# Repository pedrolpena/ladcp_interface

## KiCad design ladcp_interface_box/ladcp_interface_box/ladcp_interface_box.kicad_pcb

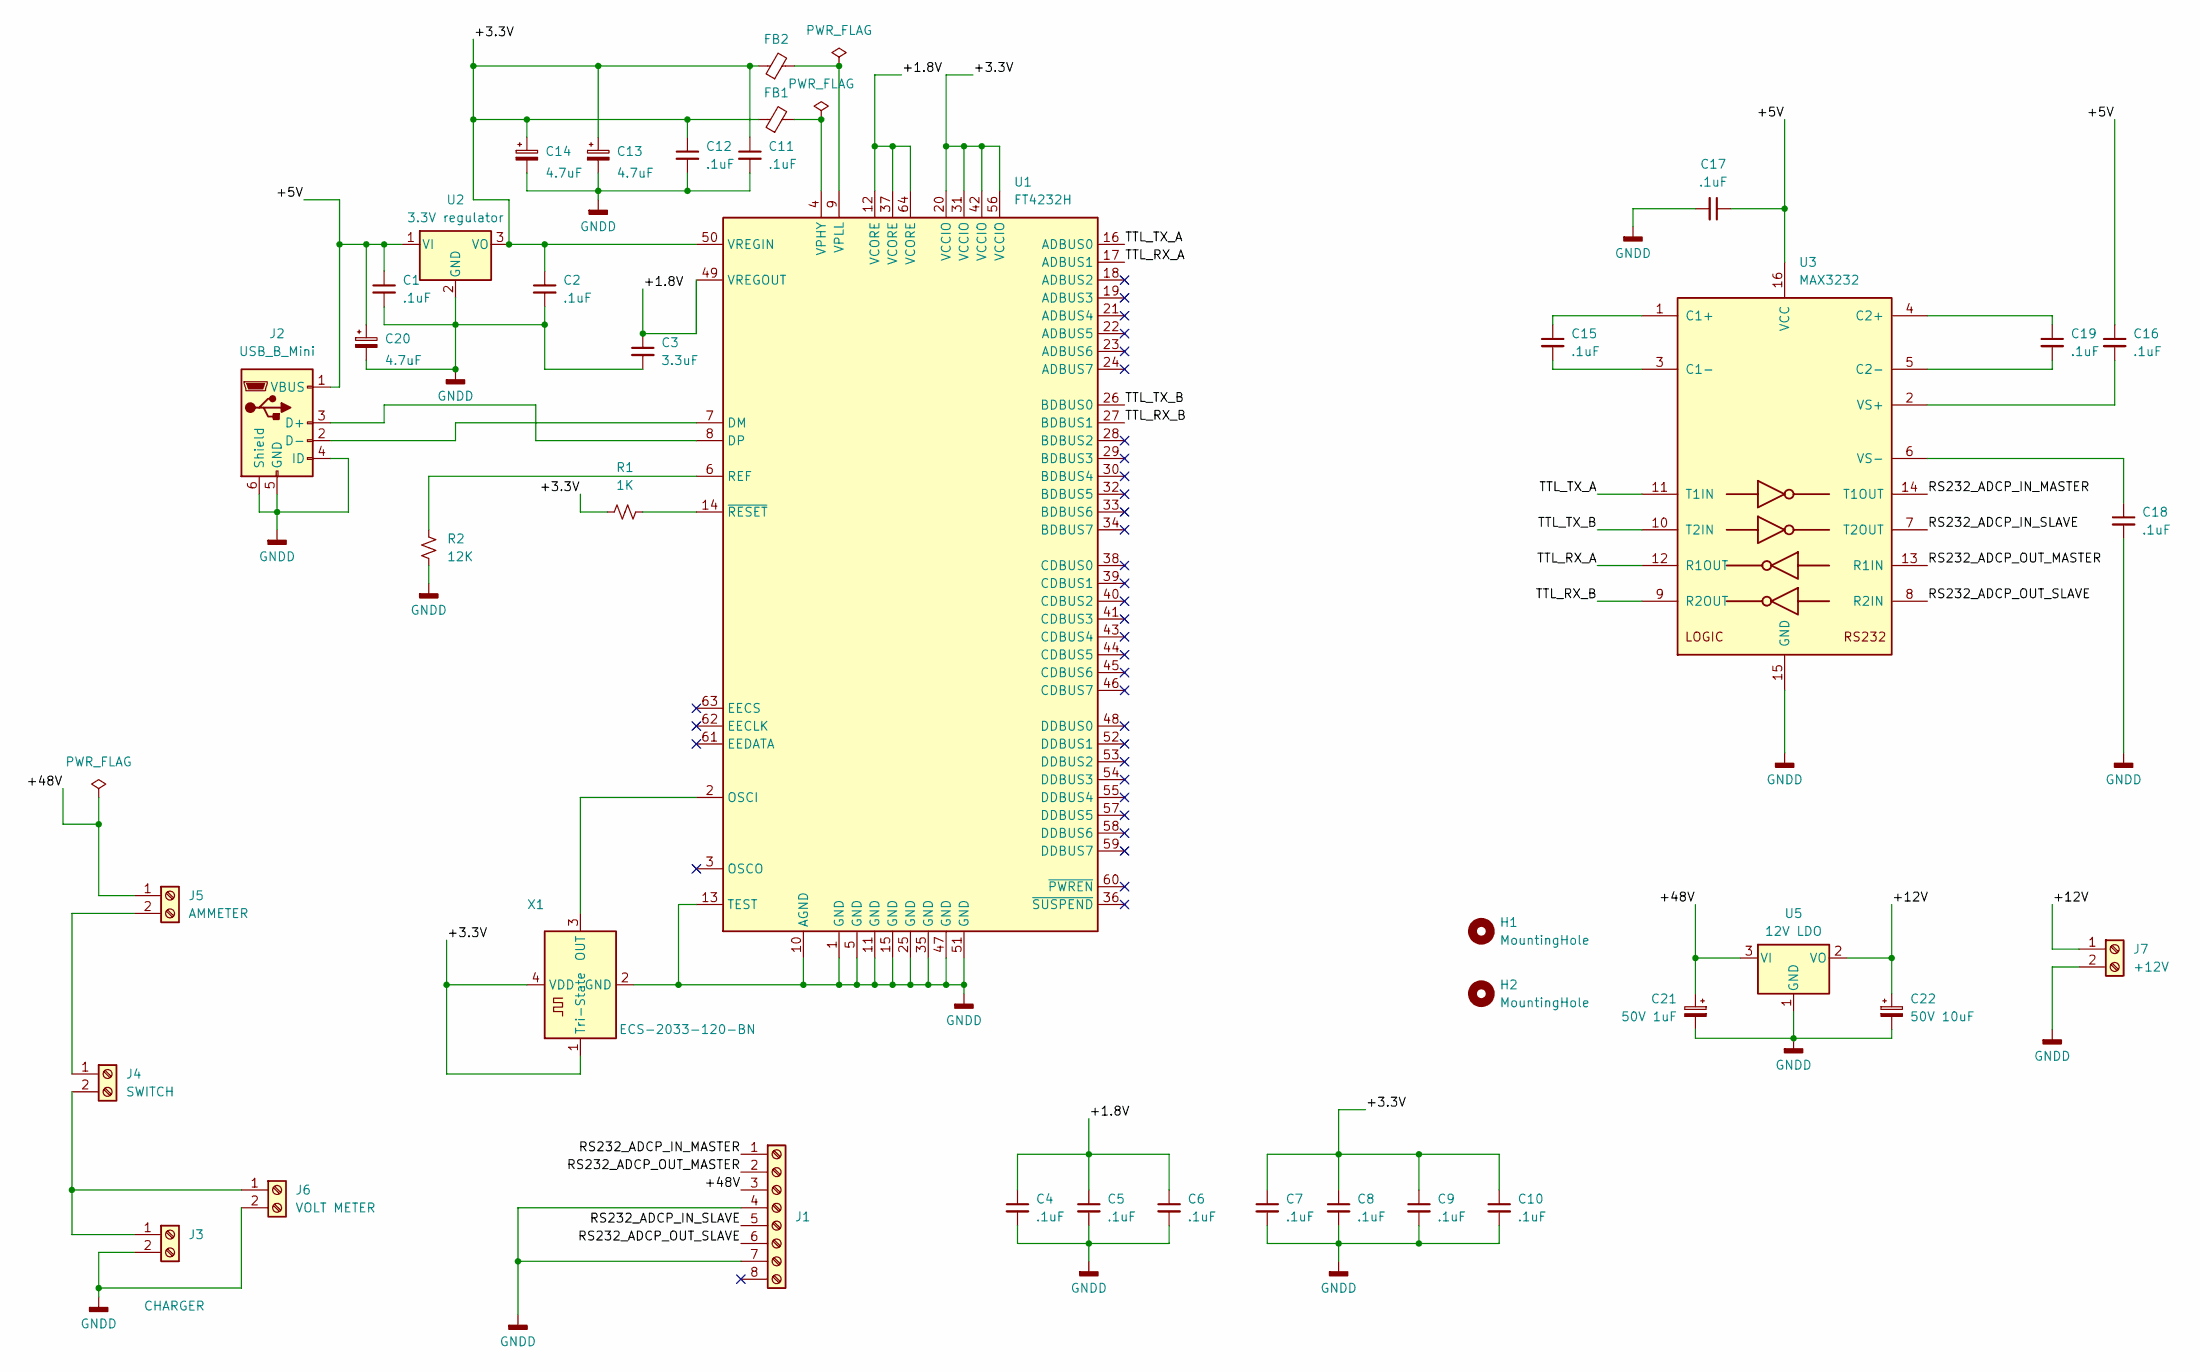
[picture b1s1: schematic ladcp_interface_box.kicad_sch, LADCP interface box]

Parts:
C1, C2, C4, C5, C6, C7, C8, C9, C10, C11, C12, C15, C16, C17, C18, C19: .1uF; C_0805_2012Metric_Pad1.18x1.45mm_HandSolder; manufacturer part# CC0805KRX7R9BB104
C3: 3.3uF; C_0805_2012Metric_Pad1.18x1.45mm_HandSolder; manufacturer part# CGA4J1X7R1E335K125AC
C13, C14, C20: 4.7uF; CP_EIA-2012-12_Kemet-R_Pad1.30x1.05mm_HandSolder; manufacturer part# TAJR475M010RNJ
C21: 50V 1uF; CP_Radial_D4.0mm_P1.50mm; manufacturer part# 105RSS050M
C22: 50V 10uF; CP_Radial_D6.3mm_P2.50mm; manufacturer part# 106RSS050M
FB1, FB2: FerriteBead_Small; L_0805_2012Metric_Pad1.15x1.40mm_HandSolder; manufacturer part# HZ0805E601R-10
H1, H2: MountingHole; MountingHole_2.1mm
J1: TERM BLK 8POS SIDE ENTRY 5MM PCB; TerminalBlock_Phoenix_PT-1,5-8-5.0-H_1x08_P5.00mm_Horizontal; manufacturer part# 1935226
J2: USB_B_Mini; USB_Mini-B_Wuerth_65100516121_Horizontal; manufacturer part# 65100516121
J3: CHARGER; TerminalBlock_Phoenix_PT-1,5-2-5.0-H_1x02_P5.00mm_Horizontal; manufacturer part# 1935161
J4: SWITCH; TerminalBlock_Phoenix_PT-1,5-2-5.0-H_1x02_P5.00mm_Horizontal; manufacturer part# 1935161
J5: AMMETER; TerminalBlock_Phoenix_PT-1,5-2-5.0-H_1x02_P5.00mm_Horizontal; manufacturer part# 1935161
J6: VOLT METER; TerminalBlock_Phoenix_PT-1,5-2-5.0-H_1x02_P5.00mm_Horizontal; manufacturer part# 1935161
J7: +12V; TerminalBlock_Phoenix_PT-1,5-2-5.0-H_1x02_P5.00mm_Horizontal; manufacturer part# 1935161
R1: 1K; R_0805_2012Metric_Pad1.20x1.40mm_HandSolder; manufacturer part# RC0805FR-071KL
R2: 12K; R_0805_2012Metric_Pad1.20x1.40mm_HandSolder; manufacturer part# RMCF0805JT12K0
U1: FT4232H; LQFP-64_10x10mm_P0.5mm; manufacturer part# FT4232HL-REEL
U2: 3.3V regulator; TO-252-3_TabPin2; manufacturer part# BA033CC0FP-E2
U3: MAX3232; TSSOP-16_4.4x5mm_P0.65mm; manufacturer part# MAX3232EUE+T
U5: 12V LDO; SOT-23; manufacturer part# ZXTR2112FQ-7
X1: ECS-2033-120-BN; Oscillator_SMD_ECS_2520MV-xxx-xx-4Pin_2.5x2.0mm; manufacturer part# ECS-2033-120-BN

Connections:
/+1.8V: C3.1, C4.1, C5.1, C6.1, U1.12 (VCORE), U1.37 (VCORE), U1.49 (VREGOUT), U1.64 (VCORE)
/+3.3V: C2.1, C7.1, C8.1, C9.1, C10.1, C11.1, C12.1, C13.1, C14.1, FB1.1, FB2.1, R1.2, U1.20 (VCCIO), U1.31 (VCCIO), U1.42 (VCCIO), U1.50 (VREGIN), U1.56 (VCCIO), U2.3 (VO), X1.1 (Tri-State), X1.4 (VDD)
/+5V: C1.1, C16.1, C17.1, C20.1, J2.1 (VBUS), U2.1 (VI), U3.16 (VCC)
/+12V: C22.1, J7.1, U5.2 (VO)
/+48V: C21.1, J1.3, J5.1, U5.3 (VI)
/RS232_ADCP_IN_MASTER: J1.1, U3.14 (T1OUT)
/RS232_ADCP_IN_SLAVE: J1.5, U3.7 (T2OUT)
/RS232_ADCP_OUT_MASTER: J1.2, U3.13 (R1IN)
/RS232_ADCP_OUT_SLAVE: J1.6, U3.8 (R2IN)
/TTL_RX_A: U1.17 (ADBUS1), U3.12 (R1OUT)
/TTL_RX_B: U1.27 (BDBUS1), U3.9 (R2OUT)
/TTL_TX_A: U1.16 (ADBUS0), U3.11 (T1IN)
/TTL_TX_B: U1.26 (BDBUS0), U3.10 (T2IN)
GNDD: C1.2, C2.2, C3.2, C4.2, C5.2, C6.2, C7.2, C8.2, C9.2, C10.2, C11.2, C12.2, C13.2, C14.2, C17.2, C18.2, C20.2, C21.2, C22.2, J1.4, J1.7, J2.4 (ID), J2.5 (GND), J2.6 (Shield), J3.2, J6.2, J7.2, R2.2, U1.1 (GND), U1.5 (GND), U1.10 (AGND), U1.11 (GND), U1.13 (TEST), U1.15 (GND), U1.25 (GND), U1.35 (GND), U1.47 (GND), U1.51 (GND), U2.2 (GND), U3.15 (GND), U5.1 (GND), X1.2 (GND)
unnamed: J2.3 (D+), U1.8 (DP)
unnamed: J2.2 (D-), U1.7 (DM)
unnamed: J3.1, J4.2, J6.1
unnamed: J4.1, J5.2
unnamed: U1.2 (OSCI), X1.3 (OUT)
unnamed: R2.1, U1.6 (REF)
unnamed: FB1.2, U1.4 (VPHY)
unnamed: FB2.2, U1.9 (VPLL)
unnamed: R1.1, U1.14 (~RESET)
unnamed: C15.1, U3.1 (C1+)
unnamed: C15.2, U3.3 (C1-)
unnamed: C19.1, U3.4 (C2+)
unnamed: C19.2, U3.5 (C2-)
unnamed: C16.2, U3.2 (VS+)
unnamed: C18.1, U3.6 (VS-)

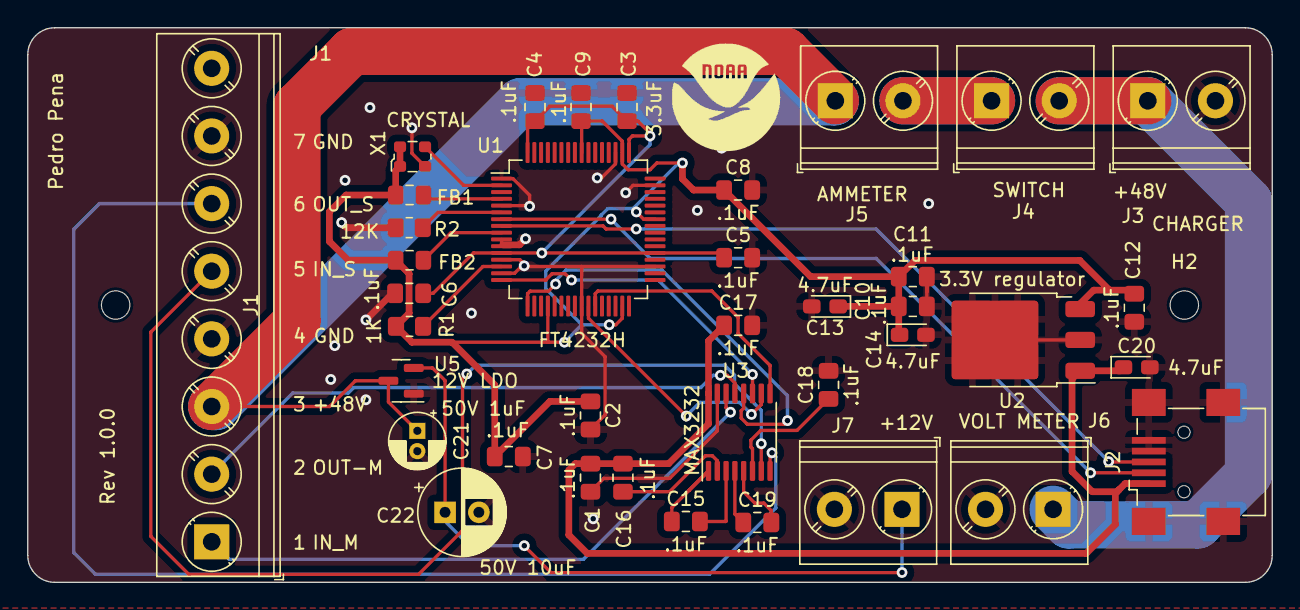
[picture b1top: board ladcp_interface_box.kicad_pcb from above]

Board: 2 copper layers, 92.0 x 41.0 mm, 40 parts (0 on the bottom side), 29 nets.

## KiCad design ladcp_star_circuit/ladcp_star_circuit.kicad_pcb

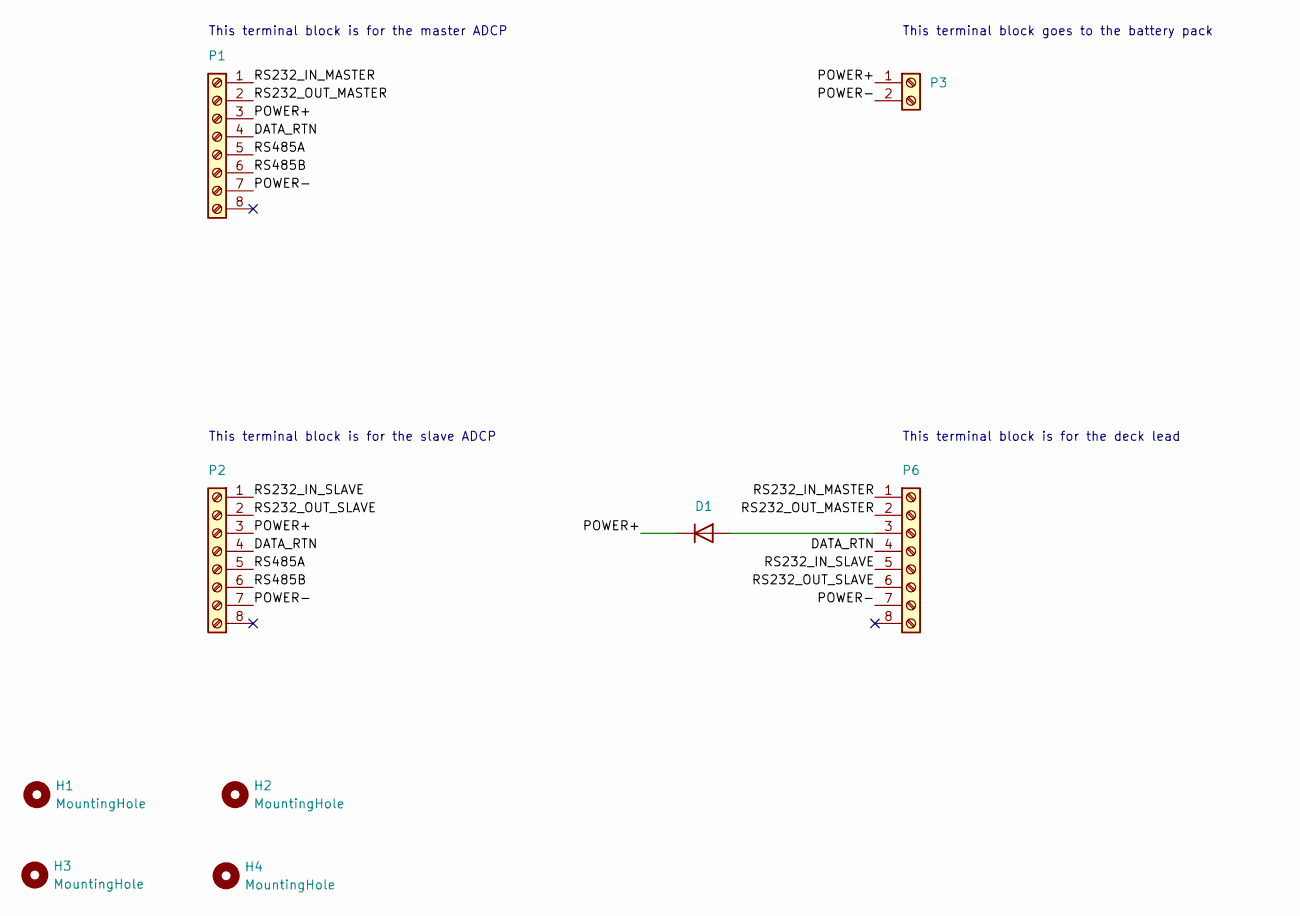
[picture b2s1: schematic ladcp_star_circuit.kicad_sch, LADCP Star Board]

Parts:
D1: P600G-E3/54; D_P600_R-6_P20.00mm_Horizontal; manufacturer part# P600G-E3/54
H1, H2, H3, H4: MountingHole; MountingHole_6.5mm
P1, P2, P6: TERM BLK 8POS SIDE ENTRY 5MM PCB; TerminalBlock_Phoenix_PT-1,5-8-5.0-H_1x08_P5.00mm_Horizontal; manufacturer part# 1935226
P3: TERM BLK 2POS SIDE ENTRY 5MM PCB; TerminalBlock_Phoenix_PT-1,5-2-5.0-H_1x02_P5.00mm_Horizontal; manufacturer part# 1935161

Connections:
/DATA_RTN: P1.4, P2.4, P6.4
/POWER+: D1.1 (K), P1.3, P2.3, P3.1
/POWER-: P1.7, P2.7, P3.2, P6.7
/RS232_IN_MASTER: P1.1, P6.1
/RS232_IN_SLAVE: P2.1, P6.5
/RS232_OUT_MASTER: P1.2, P6.2
/RS232_OUT_SLAVE: P2.2, P6.6
/RS485A: P1.5, P2.5
/RS485B: P1.6, P2.6
unnamed: D1.2 (A), P6.3

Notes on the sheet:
This terminal block is for the deck lead
This terminal block goes to the battery pack
This terminal block is for the slave ADCP
This terminal block is for the master ADCP

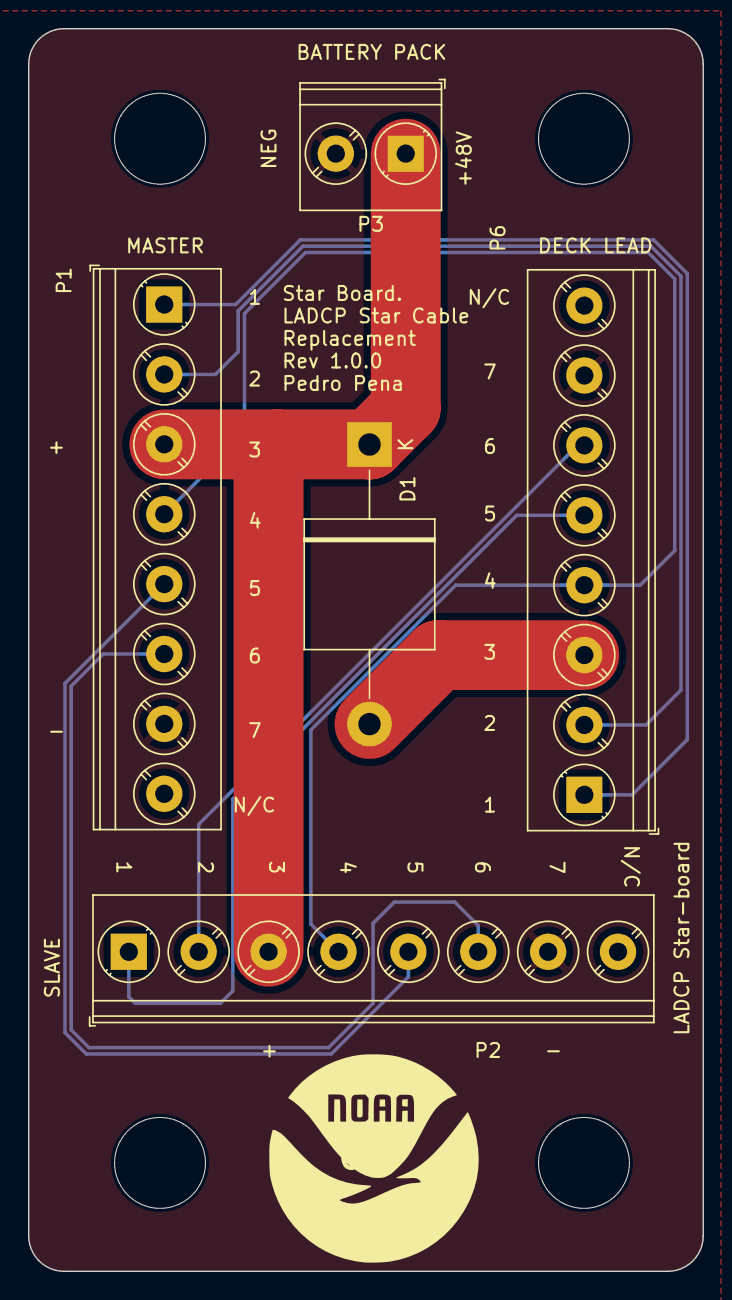
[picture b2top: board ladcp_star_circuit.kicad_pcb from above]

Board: 2 copper layers, 48.3 x 88.9 mm, 9 parts (0 on the bottom side), 10 nets.

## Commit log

2023-06-29 updated files
2023-06-30 added PCB design
2023-07-06 fixed errors
2023-07-07 removed pcb errors and warnings
2023-10-16 finished circuit
2024-03-01 added final changes
